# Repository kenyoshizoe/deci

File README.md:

# deci

100*100mm以下で作れる25キーキーパッドです。 / 25key key-pad smaller than 100\*100mm.

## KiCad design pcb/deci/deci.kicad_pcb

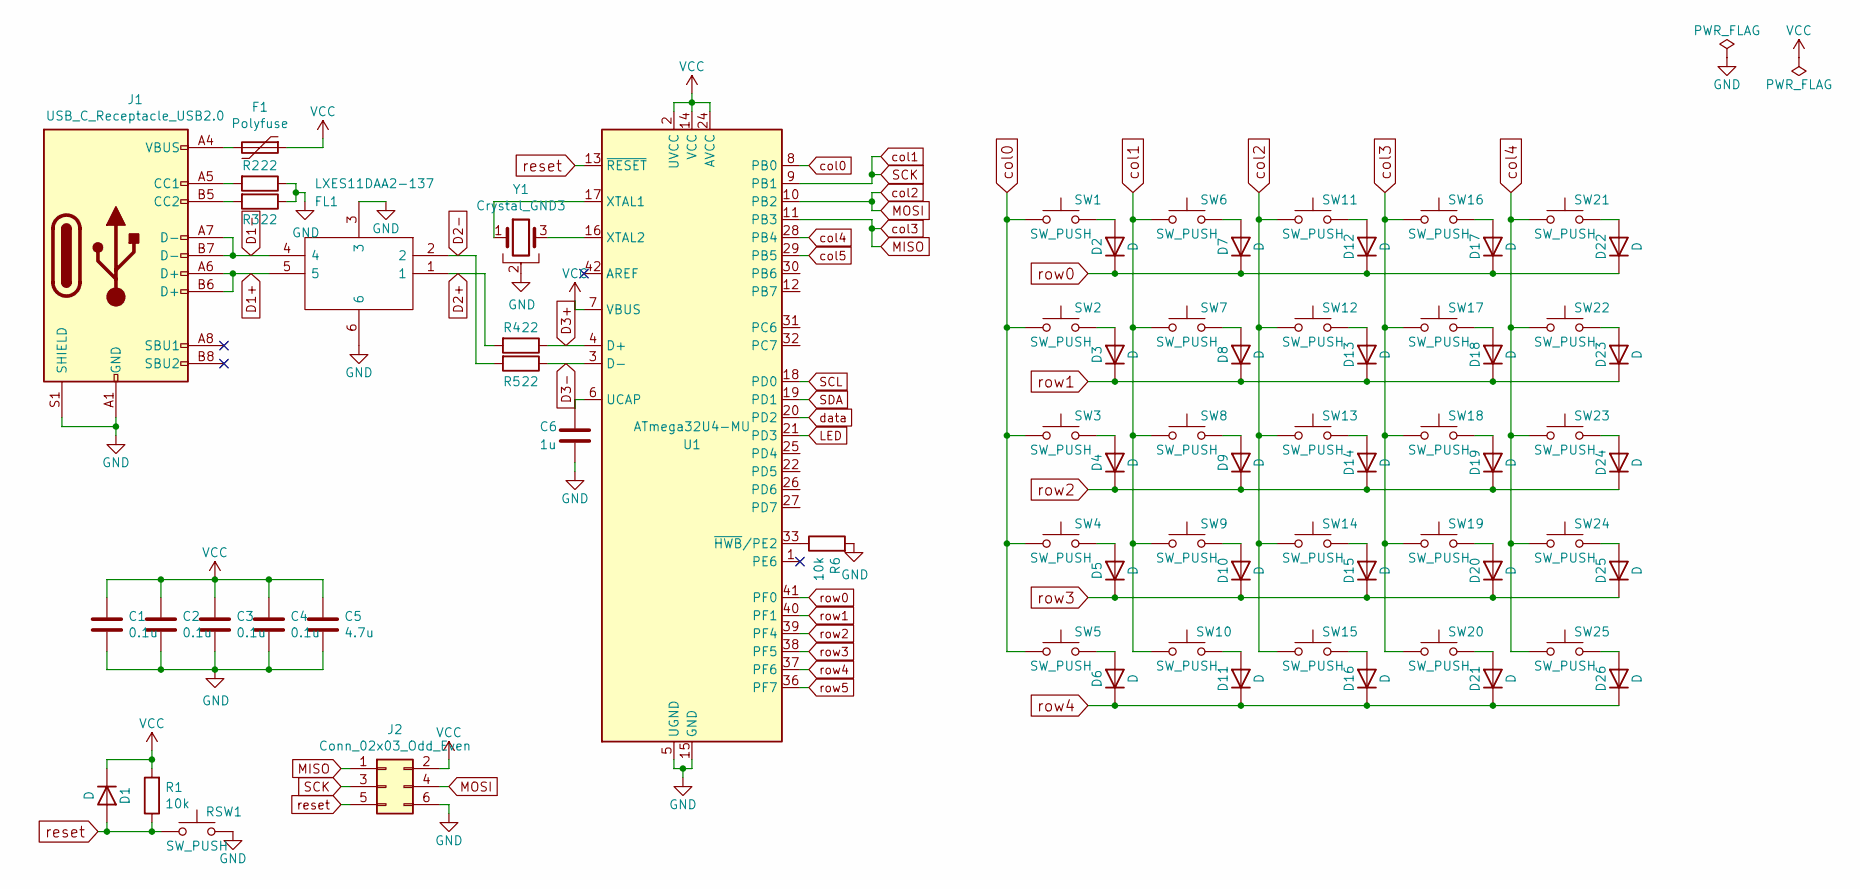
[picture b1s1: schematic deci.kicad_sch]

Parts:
C1, C2, C3, C4: 0.1u; C_0603_1608Metric_Pad1.08x0.95mm_HandSolder
C5: 4.7u; C_0603_1608Metric_Pad1.08x0.95mm_HandSolder
C6: 1u; C_0603_1608Metric_Pad1.08x0.95mm_HandSolder
D1, D2, D3, D4, D5, D6, D7, D8, D9, D10, D11, D12, D13, D14, D15, D16, D17, D18, D19, D20, D21, D22, D23, D24, D25, D26: D; D_SOD-123
F1: Polyfuse; Fuse_0603_1608Metric_Pad1.05x0.95mm_HandSolder
FL1: LXES11DAA2-137; LXES11D; Mouser Part Number 81-LXES11DAA2-137
J1: USB_C_Receptacle_USB2.0; USB_C_Receptacle_XKB_U262-16XN-4BVC11
J2: Conn_02x03_Odd_Even; PinHeader_2x03_P2.54mm_Vertical
R1, R6: 10k; R_0603_1608Metric_Pad0.98x0.95mm_HandSolder
R2, R3, R4, R5: 22; R_0603_1608Metric_Pad0.98x0.95mm_HandSolder
RSW1: SW_PUSH; THAF01-NC-R
SW1, SW2, SW3, SW4, SW5, SW6, SW7, SW8, SW9, SW10, SW11, SW12, SW13, SW14, SW15, SW16, SW17, SW18, SW19, SW20, SW21, SW22, SW23, SW24, SW25: SW_PUSH; SW_Cherry_MX_1.00u_PCB
U1: ATmega32U4-MU; LQFP-44_10x10mm_P0.8mm
Y1: Crystal_GND3; Resonator_SMD_muRata_CSTxExxV-3Pin_3.0x1.1mm_HandSoldering

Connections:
D1+: FL1.5, J1.A6 (D+), J1.B6 (D+)
D1-: FL1.4, J1.A7 (D-), J1.B7 (D-)
D2+: FL1.1, R4.2
D2-: FL1.2, R5.2
D3+: R4.1, U1.4 (D+)
D3-: R5.1, U1.3 (D-)
GND: C1.2, C2.2, C3.2, C4.2, C5.2, C6.1, FL1.3, FL1.6, J1.A1 (GND), J1.A12 (GND), J1.B1 (GND), J1.B12 (GND), J1.S1 (SHIELD), J2.6, R2.1, R3.1, R6.2, RSW1.2, U1.5 (UGND), U1.15 (GND), U1.23 (GND), U1.35 (GND), U1.43 (GND), Y1.2
LED: U1.21 (PD3)
MISO: J2.1, SW16.1, SW17.1, SW18.1, SW19.1, SW20.1, U1.11 (PB3)
MOSI: J2.4, SW11.1, SW12.1, SW13.1, SW14.1, SW15.1, U1.10 (PB2)
unnamed: C6.2, U1.6 (UCAP)
unnamed: D2.2 (A), SW1.2
unnamed: D3.2 (A), SW2.2
unnamed: D4.2 (A), SW3.2
unnamed: D5.2 (A), SW4.2
unnamed: D6.2 (A), SW5.2
unnamed: D7.2 (A), SW6.2
unnamed: D8.2 (A), SW7.2
unnamed: D9.2 (A), SW8.2
unnamed: D10.2 (A), SW9.2
unnamed: D11.2 (A), SW10.2
unnamed: D12.2 (A), SW11.2
unnamed: D13.2 (A), SW12.2
unnamed: D14.2 (A), SW13.2
unnamed: D15.2 (A), SW14.2
unnamed: D16.2 (A), SW15.2
unnamed: D17.2 (A), SW16.2
unnamed: D18.2 (A), SW17.2
unnamed: D19.2 (A), SW18.2
unnamed: D20.2 (A), SW19.2
unnamed: D21.2 (A), SW20.2
unnamed: D22.2 (A), SW21.2
unnamed: D23.2 (A), SW22.2
unnamed: D24.2 (A), SW23.2
unnamed: D25.2 (A), SW24.2
unnamed: D26.2 (A), SW25.2
unnamed: F1.2, J1.A4 (VBUS), J1.A9 (VBUS), J1.B4 (VBUS), J1.B9 (VBUS)
unnamed: J1.A5 (CC1), R2.2
unnamed: J1.B5 (CC2), R3.2
unnamed: R6.1, U1.33 (~HWB/PE2)
unnamed: U1.16 (XTAL2), Y1.3
unnamed: U1.17 (XTAL1), Y1.1
SCK: J2.3, SW6.1, SW7.1, SW8.1, SW9.1, SW10.1, U1.9 (PB1)
SCL: U1.18 (PD0)
SDA: U1.19 (PD1)
VCC: C1.1, C2.1, C3.1, C4.1, C5.1, D1.1 (K), F1.1, J2.2, R1.2, U1.2 (UVCC), U1.7 (VBUS), U1.14 (VCC), U1.24 (AVCC), U1.34 (VCC), U1.44 (AVCC)
col0: SW1.1, SW2.1, SW3.1, SW4.1, SW5.1, U1.8 (PB0)
col4: SW21.1, SW22.1, SW23.1, SW24.1, SW25.1, U1.28 (PB4)
col5: U1.29 (PB5)
data: U1.20 (PD2)
reset: D1.2 (A), J2.5, R1.1, RSW1.1, U1.13 (~RESET)
row0: D2.1 (K), D7.1 (K), D12.1 (K), D17.1 (K), D22.1 (K), U1.41 (PF0)
row1: D3.1 (K), D8.1 (K), D13.1 (K), D18.1 (K), D23.1 (K), U1.40 (PF1)
row2: D4.1 (K), D9.1 (K), D14.1 (K), D19.1 (K), D24.1 (K), U1.39 (PF4)
row3: D5.1 (K), D10.1 (K), D15.1 (K), D20.1 (K), D25.1 (K), U1.38 (PF5)
row4: D6.1 (K), D11.1 (K), D16.1 (K), D21.1 (K), D26.1 (K), U1.37 (PF6)
row5: U1.36 (PF7)

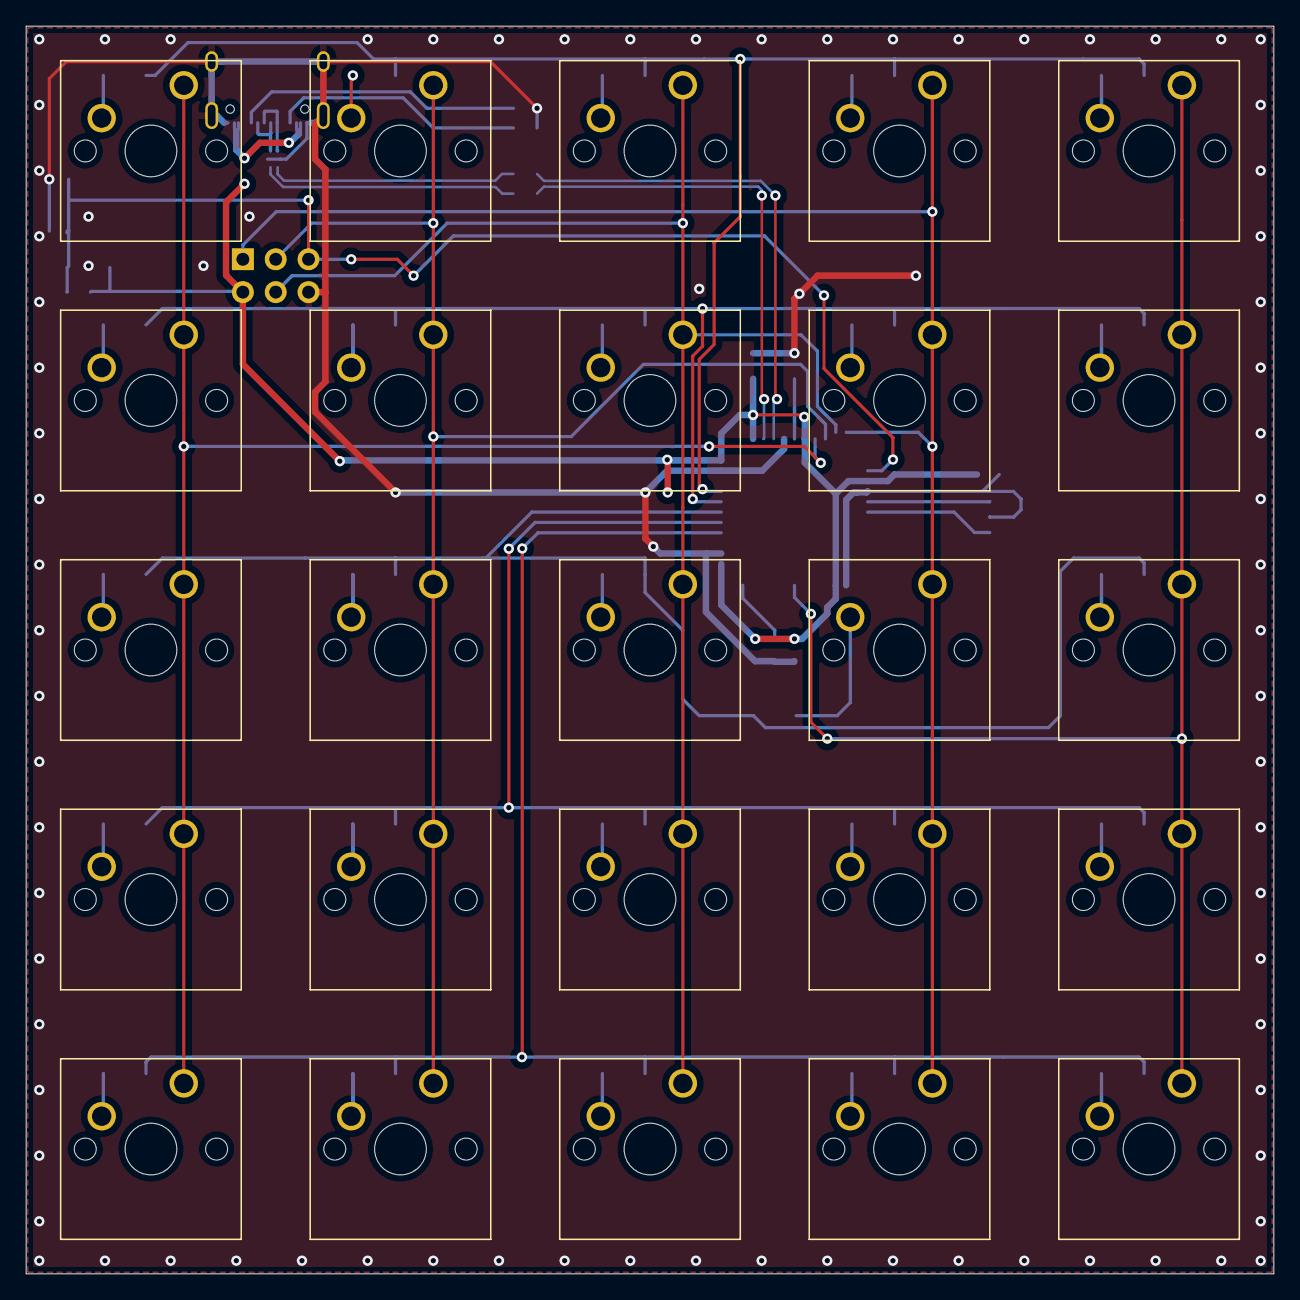
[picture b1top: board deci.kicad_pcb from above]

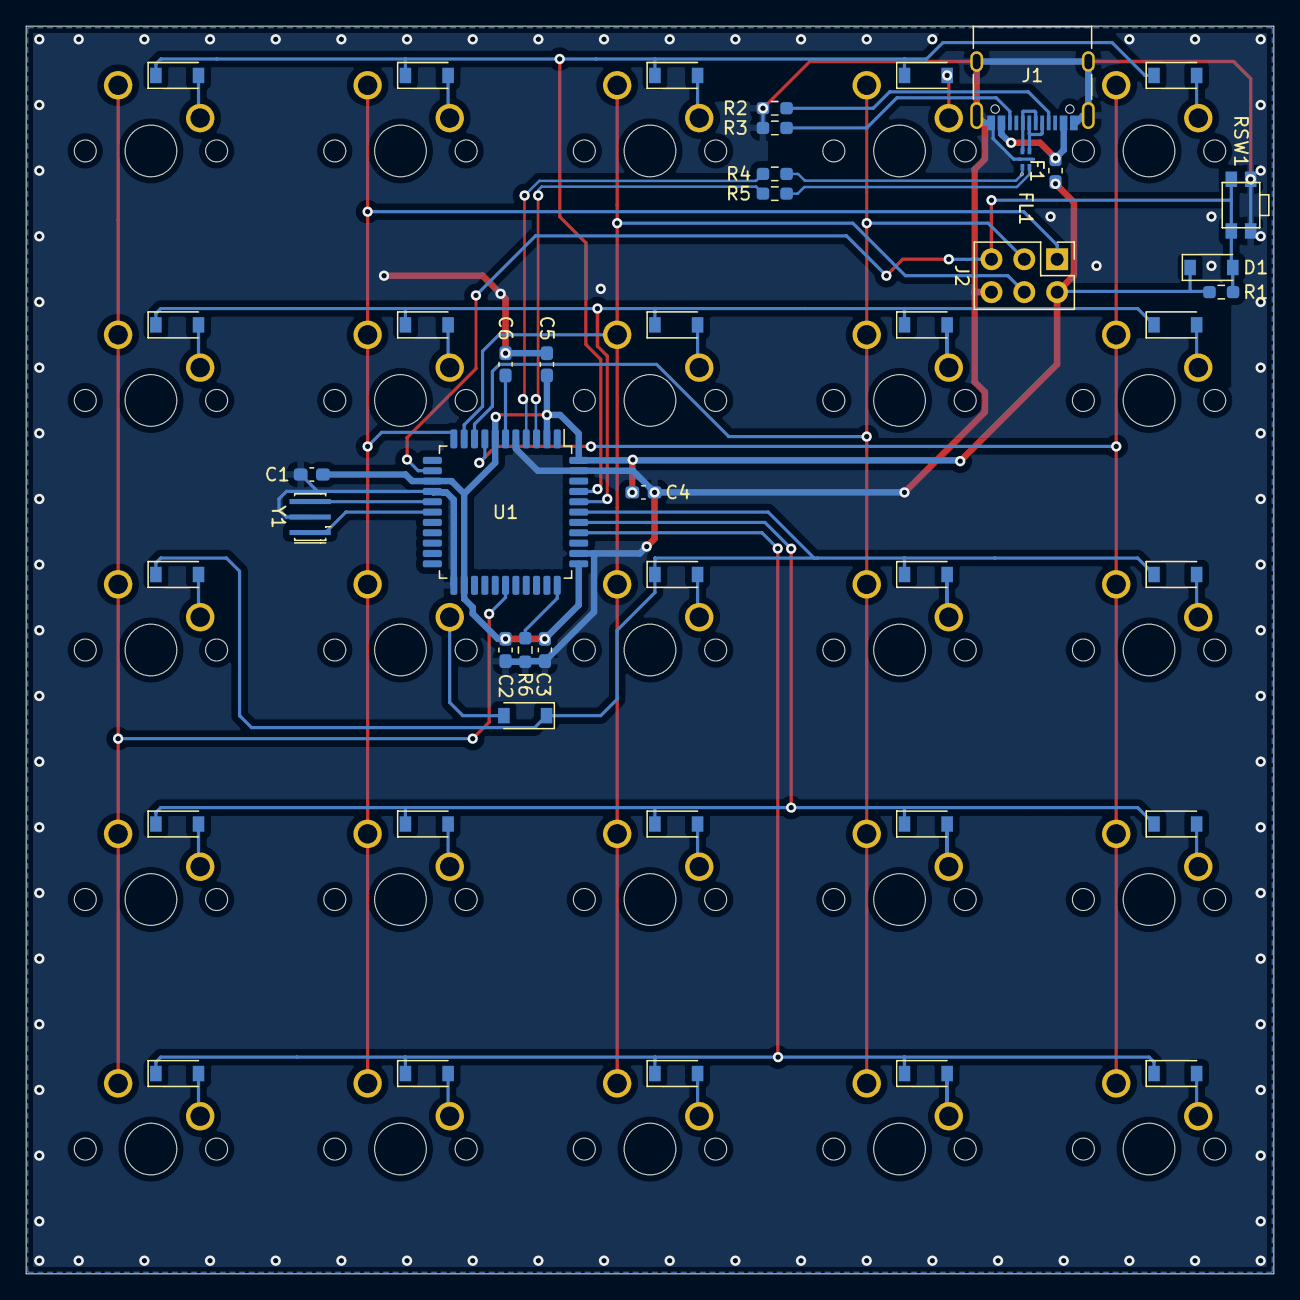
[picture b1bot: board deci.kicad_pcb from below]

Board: 2 copper layers, 96.5 x 96.5 mm, 70 parts (45 on the bottom side), 51 nets.

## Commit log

2022-10-05 :sparkles: add .gitignore for kicad
2022-10-05 :tada: add pcb
2022-10-05 :tada: add firmware
2022-10-05 :memo: add readme
